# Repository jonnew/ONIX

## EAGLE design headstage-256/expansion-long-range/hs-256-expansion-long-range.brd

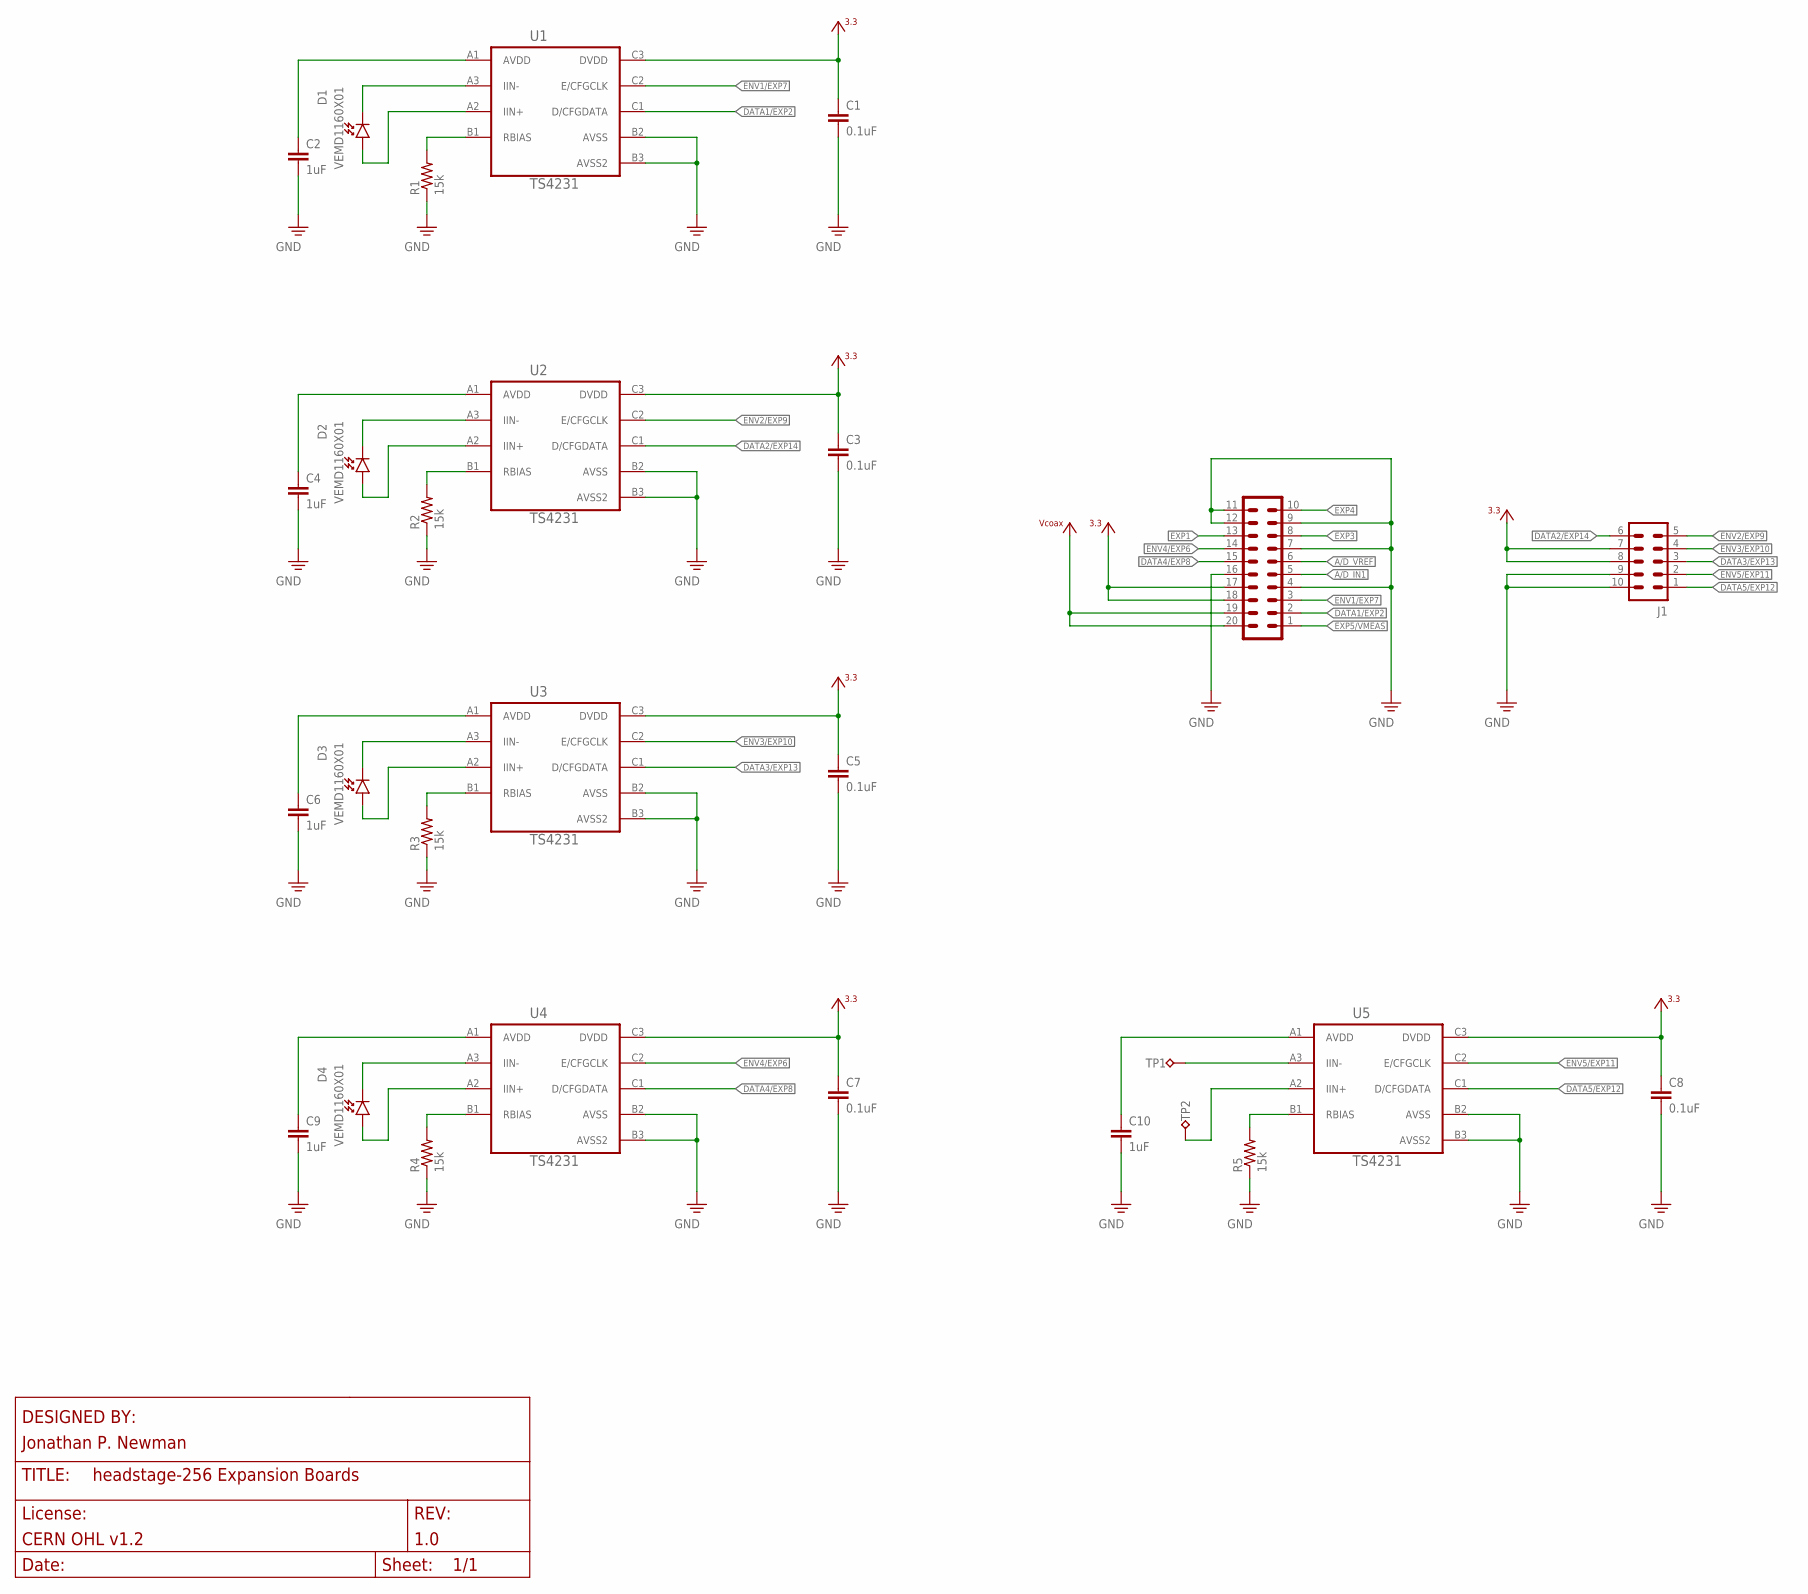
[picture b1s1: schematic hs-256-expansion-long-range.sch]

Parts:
C1, C3, C5, C7, C8: 0.1uF; 0201; PARTNO C0603X5R1C104K030BC
C2, C4, C6, C9, C10: 1uF; 0201; PARTNO CL03A105MP3ZSNH
D1, D2, D3, D4: VEMD1160X01; SFH2400FA
J1: PINHD-2X5_DF40-REC; DF40-10REC
J2: PINHD-2X10_DF40-20REC; DF40-20REC
R1, R2, R3, R4, R5: 15k; 0201
TP1, TP2: TPTP20SQ; TP20SQ
U1, U2, U3, U4, U5: TS4231; WLCSP3X3

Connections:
+3V3: C1.1, C3.1, C5.1, C7.1, C8.1, J1.7 (8), J1.8 (6), J2.17, J2.18, U1.C3 (DVDD), U2.C3 (DVDD), U3.C3 (DVDD), U4.C3 (DVDD), U5.C3 (DVDD)
A/D_IN1: J2.5
A/D_VREF: J2.6
DATA1/EXP2: J2.2, U1.C1 (D/CFGDATA)
DATA2/EXP14: J1.6 (10), U2.C1 (D/CFGDATA)
DATA3/EXP13: J1.3 (5), U3.C1 (D/CFGDATA)
DATA4/EXP8: J2.15, U4.C1 (D/CFGDATA)
DATA5/EXP12: J1.1, U5.C1 (D/CFGDATA)
ENV1/EXP7: J2.3, U1.C2 (E/CFGCLK)
ENV2/EXP9: J1.5 (9), U2.C2 (E/CFGCLK)
ENV3/EXP10: J1.4 (7), U3.C2 (E/CFGCLK)
ENV4/EXP6: J2.14, U4.C2 (E/CFGCLK)
ENV5/EXP11: J1.2 (3), U5.C2 (E/CFGCLK)
EXP1: J2.13
EXP3: J2.8
EXP4: J2.10
EXP5/VMEAS: J2.1
GND: C1.2, C2.2, C3.2, C4.2, C5.2, C6.2, C7.2, C8.2, C9.2, C10.2, J1.9 (4), J1.10 (2), J2.4, J2.7, J2.9, J2.11, J2.12, J2.16, R1.1, R2.1, R3.1, R4.1, R5.1, U1.B2 (AVSS), U1.B3 (AVSS2), U2.B2 (AVSS), U2.B3 (AVSS2), U3.B2 (AVSS), U3.B3 (AVSS2), U4.B2 (AVSS), U4.B3 (AVSS2), U5.B2 (AVSS), U5.B3 (AVSS2)
unnamed: D2.1 (C), U2.A3 (IIN-)
unnamed: D2.3 (A), U2.A2 (IIN+)
unnamed: R2.2, U2.B1 (RBIAS)
unnamed: C4.1, U2.A1 (AVDD)
unnamed: D3.1 (C), U3.A3 (IIN-)
unnamed: D3.3 (A), U3.A2 (IIN+)
unnamed: R3.2, U3.B1 (RBIAS)
unnamed: C6.1, U3.A1 (AVDD)
unnamed: D4.1 (C), U4.A3 (IIN-)
unnamed: D4.3 (A), U4.A2 (IIN+)
unnamed: R4.2, U4.B1 (RBIAS)
unnamed: C9.1, U4.A1 (AVDD)
unnamed: TP1.TP, U5.A3 (IIN-)
unnamed: TP2.TP, U5.A2 (IIN+)
unnamed: R5.2, U5.B1 (RBIAS)
unnamed: C10.1, U5.A1 (AVDD)
unnamed: D1.1 (C), U1.A3 (IIN-)
unnamed: D1.3 (A), U1.A2 (IIN+)
unnamed: R1.2, U1.B1 (RBIAS)
unnamed: C2.1, U1.A1 (AVDD)
VCOAX: J2.19, J2.20

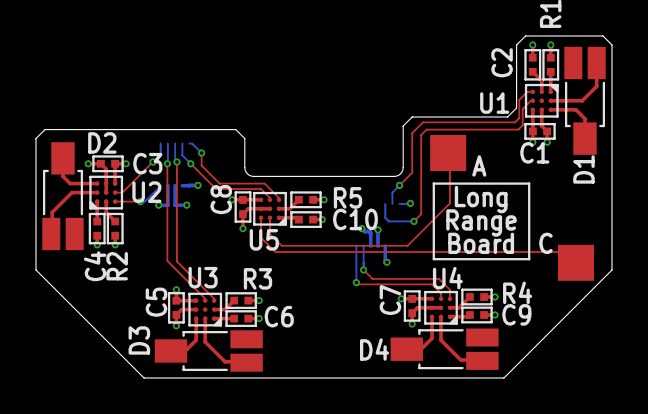
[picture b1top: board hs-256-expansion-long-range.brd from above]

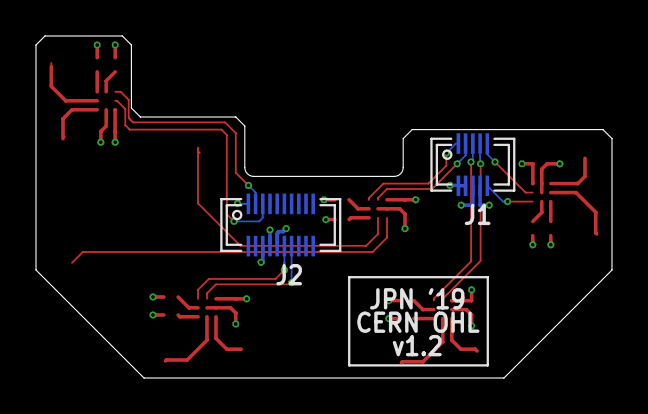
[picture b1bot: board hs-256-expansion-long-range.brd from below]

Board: 4 copper layers, 32.0 x 19.0 mm, 28 parts (2 on the bottom side), 33 nets.

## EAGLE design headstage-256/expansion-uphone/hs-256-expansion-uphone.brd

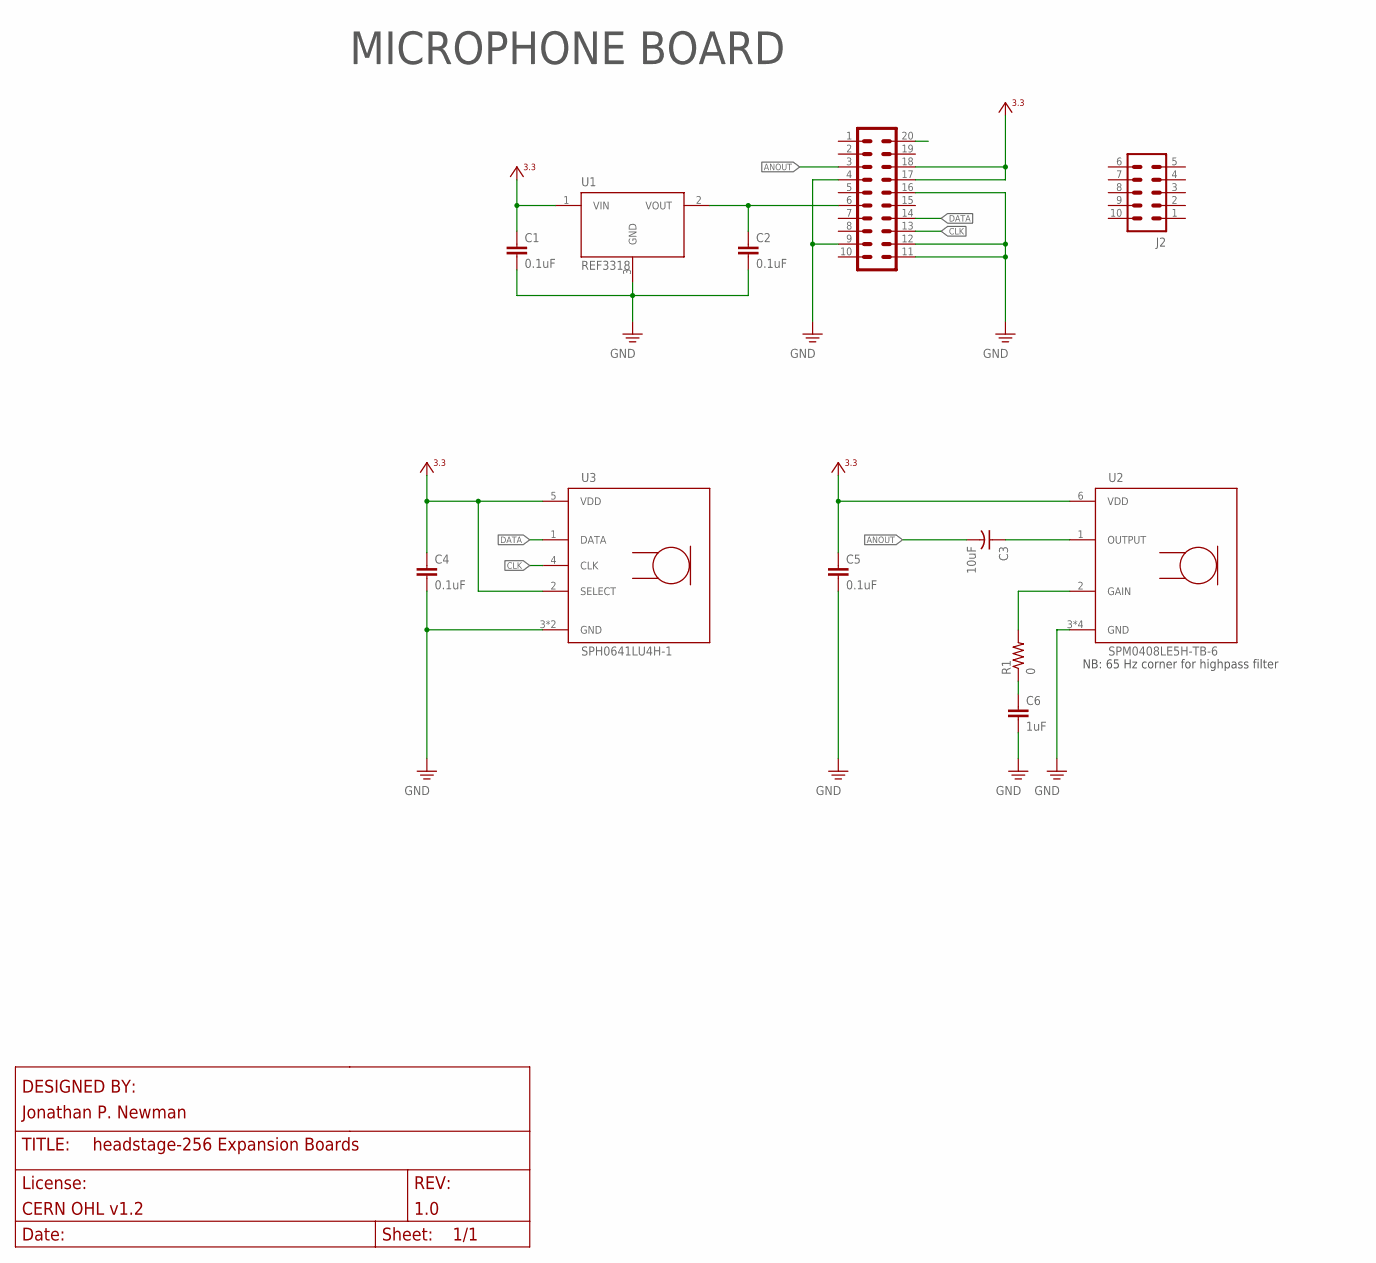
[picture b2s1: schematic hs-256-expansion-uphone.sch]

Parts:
C1, C2, C4, C5: 0.1uF; 0402
C3: 10uF; 0805-POL
C6: 1uF; 0402
J1: PINHD-2X10_DF40-20REC; DF40-20REC
J2: PINHD-2X5_DF40-REC; DF40-10REC
R1: 0; 0402
U1: REF3318; SOT23
U2: SPM0408LE5H-TB-6; KNOWLES-SPM
U3: SPH0641LU4H-1; KNOWLES-SPH

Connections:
+3V3: C1.1, C4.1, C5.1, J1.17, J1.18, U1.1 (VIN), U2.6 (VDD), U3.2 (SELECT), U3.5 (VDD)
ANOUT: C3.C (-), J1.3
CLK: J1.13, U3.4 (CLK)
DATA: J1.14, U3.1 (DATA)
GND: C1.2, C2.2, C4.2, C5.2, C6.2, J1.4, J1.9, J1.11, J1.12, J1.16, U1.3 (GND), U2.3 (GND), U2.4 (GND), U2.5 (GND), U2.7 (GND), U3.3 (GND), U3.6 (GND)
unnamed: C6.1, R1.1
unnamed: R1.2, U2.2 (GAIN)
unnamed: C3.A (+), U2.1 (OUTPUT)
VREF: C2.1, J1.6, U1.2 (VOUT)

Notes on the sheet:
NB: 65 Hz corner for highpass filter
MICROPHONE BOARD

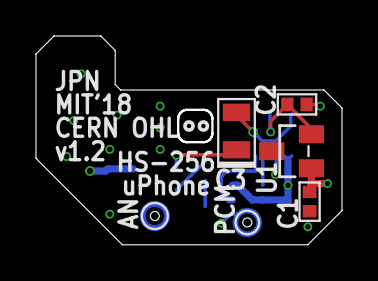
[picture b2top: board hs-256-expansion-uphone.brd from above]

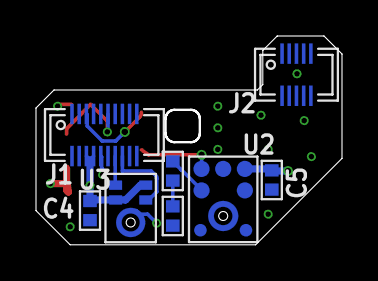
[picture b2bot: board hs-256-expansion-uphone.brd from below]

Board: 4 copper layers, 17.0 x 11.6 mm, 12 parts (8 on the bottom side), 9 nets.

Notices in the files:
headstage-256/expansion-long-range/hs-256-expansion-long-range.brd:
CERN OHL
headstage-256/expansion-long-range/hs-256-expansion-long-range.sch:
LICENSE: CERN OHL v1.2
headstage-256/headstage-256.brd:
CERN OHL 1.2
headstage-64/headstage-64-coax-adapter.brd:
CERN OHL v1.2
headstage-64/headstage-64_bga.brd:
CC-BY-SA
headstage-64/headstage-64_bga.sch:
LICENSE: CC-BY-SA-4.0
